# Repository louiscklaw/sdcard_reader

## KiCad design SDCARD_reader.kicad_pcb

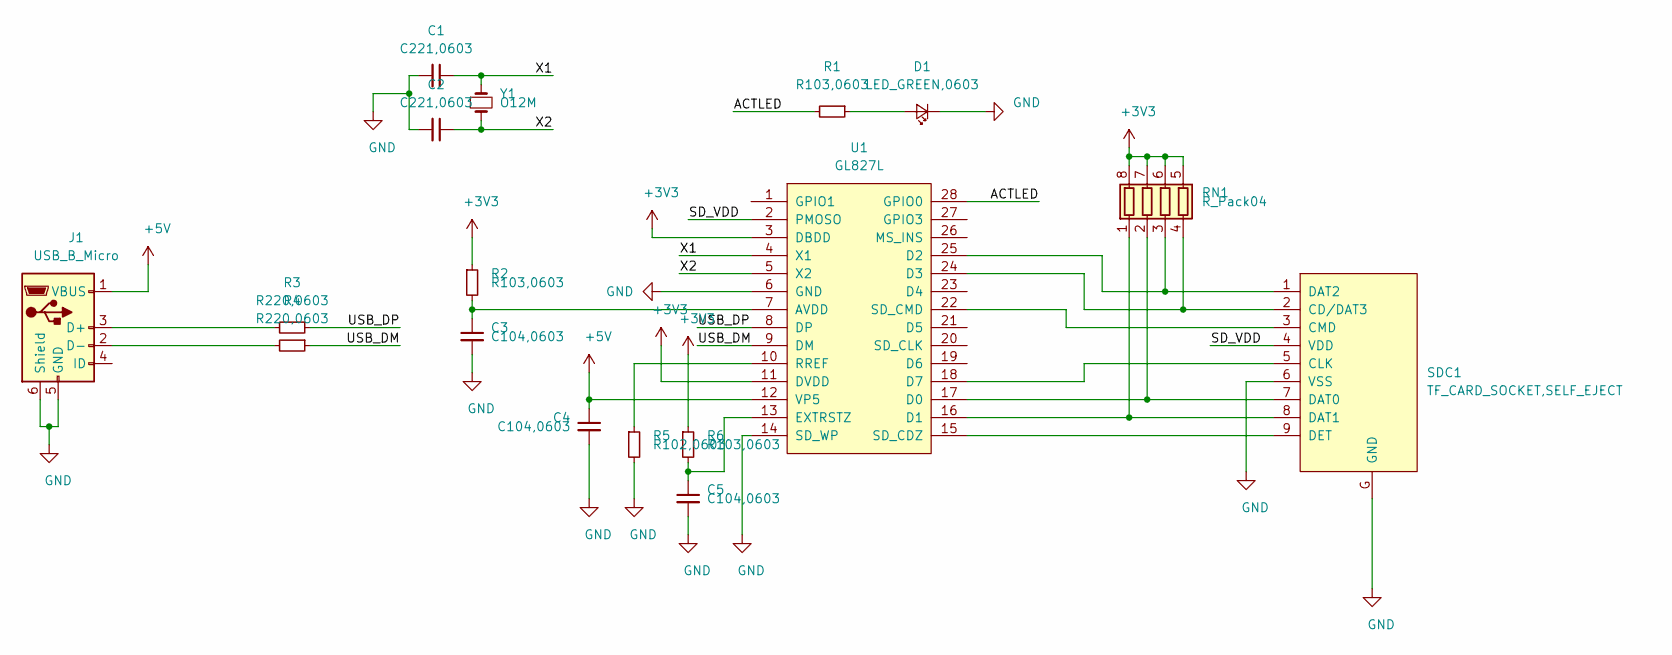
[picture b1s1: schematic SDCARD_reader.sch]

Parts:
C1, C2: C221,0603; C_0603_1608Metric_Pad1.05x0.95mm_HandSolder
C3, C4, C5: C104,0603; C_0603_1608Metric_Pad1.05x0.95mm_HandSolder
D1: LED_GREEN,0603; LED_0603_1608Metric_Pad1.05x0.95mm_HandSolder
J1: USB_B_Micro; USB_Micro-B_Molex_47346-0001
R1, R2, R6: R103,0603; R_0603_1608Metric_Pad1.05x0.95mm_HandSolder
R3, R4: R220,0603; R_0603_1608Metric_Pad1.05x0.95mm_HandSolder
R5: R102,0603; R_0603_1608Metric_Pad1.05x0.95mm_HandSolder
RN1: R_Pack04; R_Array_Convex_4x0603
SDC1: TF_CARD_SOCKET,SELF_EJECT; SUNTECH_ST-TF-003A
U1: GL827L; SSOP-28_3.9x9.9mm_P0.635mm
Y1: O12M; crystal_hc-49s

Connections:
+3V3: R2.1, R6.1, RN1.5 (R4.2), RN1.6 (R3.2), RN1.7 (R2.2), RN1.8 (R1.2), U1.3 (DBDD), U1.11 (DVDD)
+5V: C4.1, J1.1 (VBUS), U1.12 (VP5)
/ACTLED: R1.2, U1.28 (GPIO0)
/SD_VDD: SDC1.4 (VDD), U1.2 (PMOSO)
/USB_DM: R4.1, U1.9 (DM)
/USB_DP: R3.1, U1.8 (DP)
/X1: C1.1, U1.4 (X1), Y1.1
/X2: C2.1, U1.5 (X2), Y1.2
unnamed: C3.1, R2.2, U1.7 (AVDD)
unnamed: C5.1, R6.2, U1.13 (EXTRSTZ)
unnamed: D1.2 (A), R1.1
unnamed: J1.2 (D-), R4.2
unnamed: J1.3 (D+), R3.2
unnamed: R5.1, U1.10 (RREF)
unnamed: RN1.1 (R1.1), SDC1.8 (DAT1), U1.16 (D1)
unnamed: RN1.2 (R2.1), SDC1.7 (DAT0), U1.17 (D0)
unnamed: RN1.3 (R3.1), SDC1.1 (DAT2), U1.25 (D2)
unnamed: RN1.4 (R4.1), SDC1.2 (CD/DAT3), U1.24 (D3)
unnamed: SDC1.3 (CMD), U1.22 (SD_CMD)
unnamed: SDC1.5 (CLK), U1.18 (D7)
unnamed: SDC1.9 (DET), U1.15 (SD_CDZ)

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
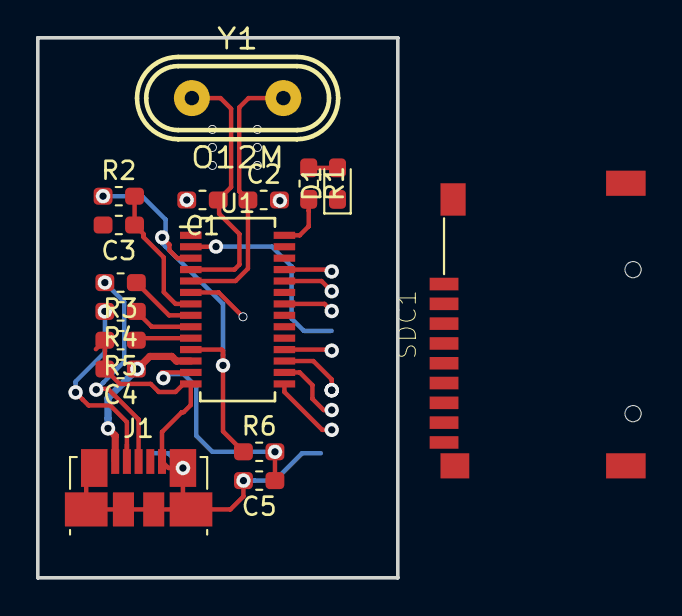
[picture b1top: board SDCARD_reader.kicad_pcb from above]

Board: 2 copper layers, 20.0 x 30.0 mm, 16 parts (0 on the bottom side), 22 nets.

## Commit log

2018-12-16 update,
2020-05-07 ci: init travis build config,
2020-05-07 ci: init travis token,
